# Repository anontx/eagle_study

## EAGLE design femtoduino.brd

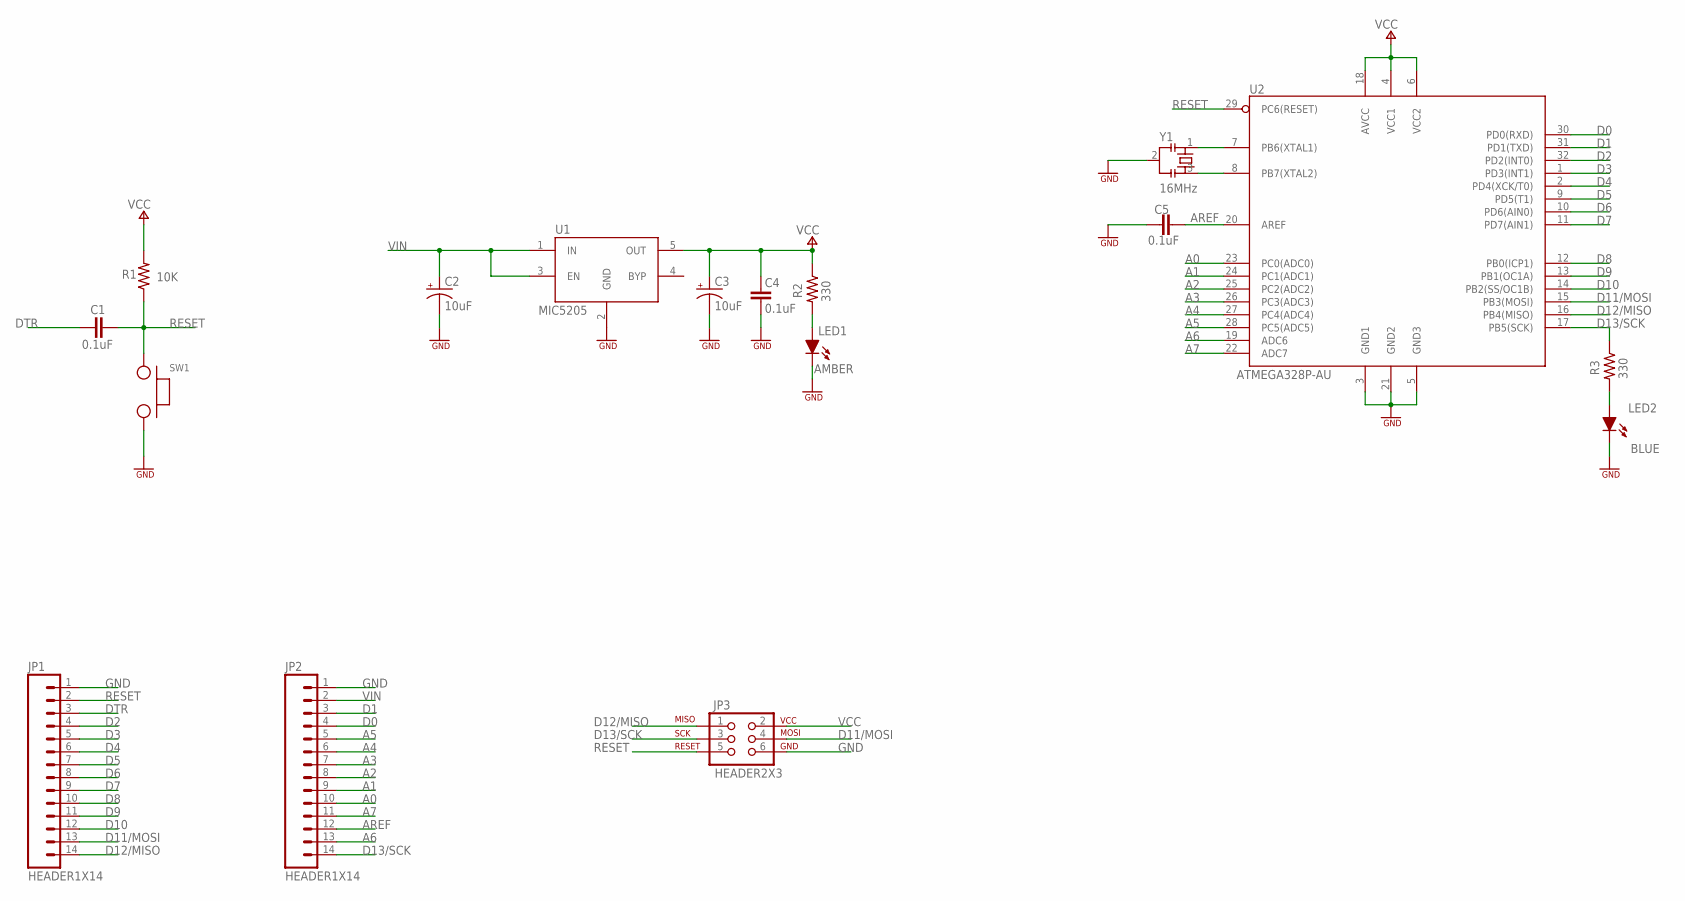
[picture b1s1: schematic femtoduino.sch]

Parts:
C1, C4, C5: 0.1uF; SMD0603
C2, C3: 10uF; EIA3216
JP1, JP2: HEADER1X14; 1X14
JP3: HEADER2X3; 2X3
LED1: AMBER; LED_0603
LED2: BLUE; LED_0603
R1: 10K; SMD0603
R2, R3: 330; SMD0603
SW1: SWITCH; SWITCH-SPST
U1: MIC5205; SOT23-5
U2: ATMEGA328P-AU; TQFP32
Y1: 16MHz; CSTCE

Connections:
A0: JP2.10, U2.23 (PC0(ADC0))
A1: JP2.9, U2.24 (PC1(ADC1))
A2: JP2.8, U2.25 (PC2(ADC2))
A3: JP2.7, U2.26 (PC3(ADC3))
A4: JP2.6, U2.27 (PC4(ADC4))
A5: JP2.5, U2.28 (PC5(ADC5))
A6: JP2.13, U2.19 (ADC6)
A7: JP2.11, U2.22 (ADC7)
AREF: C5.1, JP2.12, U2.20 (AREF)
D0: JP2.4, U2.30 (PD0(RXD))
D1: JP2.3, U2.31 (PD1(TXD))
D2: JP1.4, U2.32 (PD2(INT0))
D3: JP1.5, U2.1 (PD3(INT1))
D4: JP1.6, U2.2 (PD4(XCK/T0))
D5: JP1.7, U2.9 (PD5(T1))
D6: JP1.8, U2.10 (PD6(AIN0))
D7: JP1.9, U2.11 (PD7(AIN1))
D8: JP1.10, U2.12 (PB0(ICP1))
D9: JP1.11, U2.13 (PB1(OC1A))
D10: JP1.12, U2.14 (PB2(SS/OC1B))
D11/MOSI: JP1.13, JP3.4, U2.15 (PB3(MOSI))
D12/MISO: JP1.14, JP3.1, U2.16 (PB4(MISO))
D13/SCK: JP2.14, JP3.3, R3.1, U2.17 (PB5(SCK))
DTR: C1.1, JP1.3
GND: C2.C (-), C3.C (-), C4.2, C5.2, JP1.1, JP2.1, JP3.6, LED1.C, LED2.C, SW1.2, U1.2 (GND), U2.3 (GND1), U2.5 (GND3), U2.21 (GND2), Y1.2
unnamed: LED1.A, R2.2
unnamed: U2.7 (PB6(XTAL1)), Y1.1
unnamed: U2.8 (PB7(XTAL2)), Y1.3
unnamed: LED2.A, R3.2
RESET: C1.2, JP1.2, JP3.5, R1.1, SW1.1, U2.29 (PC6(RESET))
VCC: C3.A (+), C4.1, JP3.2, R1.2, R2.1, U1.5 (OUT), U2.4 (VCC1), U2.6 (VCC2), U2.18 (AVCC)
VIN: C2.A (+), JP2.2, U1.1 (IN), U1.3 (EN)

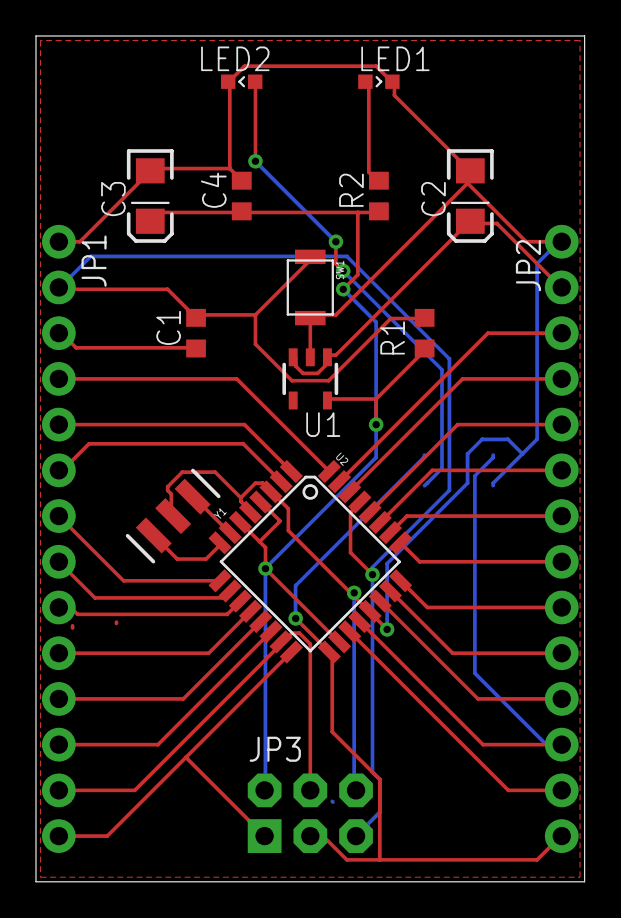
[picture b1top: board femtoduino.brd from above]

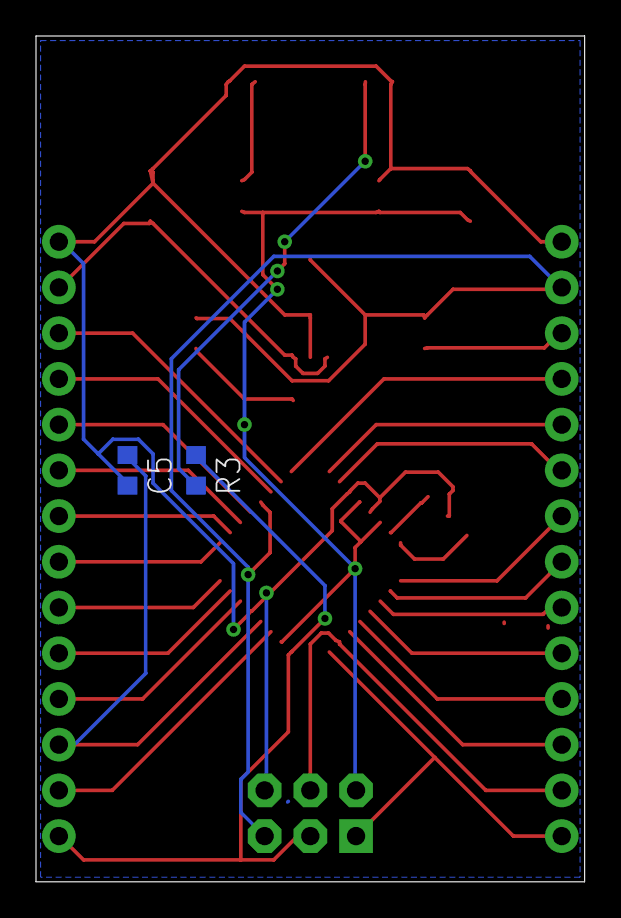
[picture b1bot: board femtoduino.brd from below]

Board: 2 copper layers, 30.5 x 47.0 mm, 17 parts (2 on the bottom side), 32 nets.

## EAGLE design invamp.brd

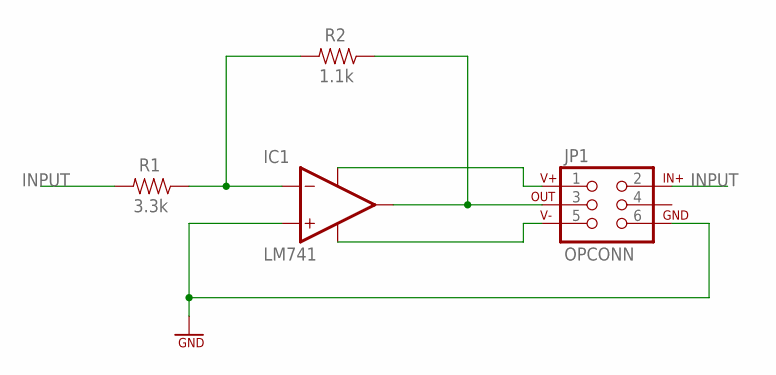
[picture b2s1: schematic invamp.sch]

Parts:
IC1: LM741; SO08
JP1: OPCONN; 2X3
R1: 3.3k; SMD0603
R2: 1.1k; SMD0603

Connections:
GND: IC1.3 (IN+), JP1.6
INPUT: JP1.2, R1.2
unnamed: IC1.2 (IN-), R1.1, R2.2
unnamed: IC1.6 (OUT), JP1.3, R2.1
unnamed: IC1.7 (V+), JP1.1
unnamed: IC1.4 (V-), JP1.5

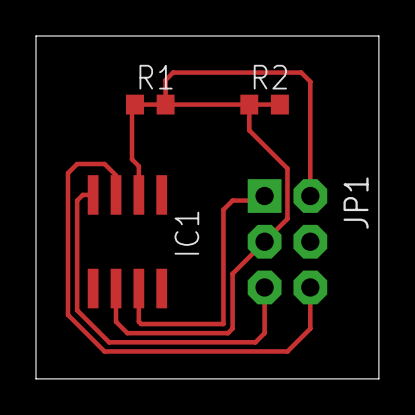
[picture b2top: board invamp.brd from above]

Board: 2 copper layers, 19.1 x 19.1 mm, 4 parts (0 on the bottom side), 6 nets.

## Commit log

2016-08-06 invamp
2016-08-06 femtoduino sch
2016-08-06 add femtoduino brd
2016-08-06 routing
2016-08-07 simple & vacuum
